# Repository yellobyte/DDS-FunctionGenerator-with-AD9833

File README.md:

# DDS Function Generator with AD9833 module #

While doing some work on Audio Amplifiers and Light Organs in 2016 I needed a simple (and not necessarily absolutely precise) **Function Generator** to generate sinus signals in the frequency range of 10Hz...30kHz and voltage levels of about 0.7...1Vrms. All devices I needed to test had input impedances in the range of ~2kOhm...20kOhm. 
  
Unfortunately I didn't call a function generator my own. So in order to have some additional fun, putting together one by myself instead of buying one on the internet was the only option. I ended up with a device able to generate output signals with the following specifications:

 - **Sinus/Triangle, amplitude 0.01 to 6.00 Vpp, frequency 1Hz to 500kHz**
 - **TTL, amplitude 5 Vpp, frequency 1Hz to 5.0 MHz**
 
 Switching waveform, output level and frequency is done with 2 front panel knobs: a pushbutton switch labelled "Select" and a simple rotary encoder with push switch labelled "Modify". The display is a standard 16x2 LCD (HD44780) having a small I2C-LCD adapter module (PCF8574 I/O expander) mounted piggyback.

All components were put into an enclosure UM 52011-L from [Bopla](https://www.bopla.de/en/enclosure-technology/product/ultramas/enclosure-with-air-vents/um-52011-l.html) which had exactly the size needed.
  
### Front side with 2 controls, 16x2 LCD display and BNC output socket: ###

The two controls allow to change signal [waveform](https://github.com/yellobyte/DDS-FunctionGenerator-with-AD9833/raw/main/Doc/SettingWaveform.mp4), output [level](https://github.com/yellobyte/DDS-FunctionGenerator-with-AD9833/raw/main/Doc/SettingLevel+SwitchingBetweenVppVrms.mp4) (Vpp resp. Vrms for sinus/triangle) and [frequency](https://github.com/yellobyte/DDS-FunctionGenerator-with-AD9833/raw/main/Doc/SettingFrequency.mp4) very quickly. Have a look at folder [**Doc**](https://github.com/yellobyte/DDS-FunctionGenerator-with-AD9833/blob/main/Doc) to find more details. 
  
## General technical info ##

The analog part of the circuitry is shielded in tin plate (an old coffee tin proved ideal for this purpose, you will recognize my favorite Italian coffee brand) to keep the output signal as clear as possible and reduce EMI. 
  
The settings for waveform/level/frequency get stored in EEPROM of the Atmega168A and therefore stay permanent even after switching the device off/on.

By default, turning the encoder knob will change the output signal immediately. For example, changing the output level from 0.5Vpp up to 6.00Vpp requires a few full turns of the knob and therefore will take a few seconds. Means the output level will rise steadily.
  
However, sometimes, when testing the automatic gain control (AGC) of audio input stages for example, it requires a signal that rises instantaneously . No problem! Switch off the device and have the encoder knob pressed for two seconds while switching power back on. After that, changing a single setting (waveform, level or frequency) on the display will not affect the output signal. Only after pressing the knob shortly (<0.5s) will the new setting appear at the output.

### Some circuit details ###
    
The DDS module (available for only a few dollars on Ebay/Ali/etc.) uses a sophisticated programmable waveform generator IC [AD9833](https://www.analog.com/en/products/ad9833.html) with 0...12.5MHz output frequency rate. 
  
Unfortunately the output pin of the AD9833 chip on the small **DDS module** shipped from Asia was galvanically isolated from the modules output pin (due to C8/C9). The quickest remedy was to bridge one of the two capacitors with a short wire, as you can see on the [**board**](https://github.com/yellobyte/DDS-FunctionGenerator-with-AD9833/raw/main/Doc/Board_V1.0_top.jpg) or below in the modules schematic. Apart from that the module was perfect for the task.

The AD9833 is written to via SPI interface. The internet provides ready to use libraries for it but I decided to use some small, quick and dirty code for only two features are needed: setting frequency & waveform.
  
The output signal of the AD9833 is unipolar and has a constant amplitude  of +38mV...+650mV over the full frequency range. The combination of Opamps IC3 + IC5 converts it to a bipolar, symmetrical signal with constant amplitude +/- 3.0V (6Vpp).  

The combination DAC1/IC6/IC7 is then used to attenuate this signal to the desired output level. The DAC IC [AD5452](https://www.analog.com/en/products/ad5452.html) contains a 12-bit R-2R-ladder and simply sets the amplification factor (better to say attenuation factor) of the combination IC6 (Opamp) + IC7 (unity gain buffer). To set the output level the selected value (0.01...6.00Vpp resp. its equivalent in Vrms) gets translated into a 12-bit value (range 0...4095) and then written to the DAC via SPI bus.

The [LMH6321](https://www.ti.com/product/LMH6321) (IC7) acts as output driver/buffer with gain=1 (unity gain) and features an  "adjustable current limit". Resistor R16 sets this limit to roughly 110mA for thermal protection in case of a short at the BNC output socket.
  
Capacitors C20/C22/C38 are not populated because the Opamp [NE5534](https://www.ti.com/product/NE5534) (IC6) showed sufficient results without them. In case you want to increase the maximum analog output frequency and try different Opamps for best results you might need them.

The two 100 Ohm resistors R9/R14 in parallel at the IC7 driver output were designed into the schematic and soldered on the board but shorted with wire in the end because the device will solely get connected to audio devices with a few 1..10kOhm input impedance and only generates audio resp. low analog frequency signals anyway. Means it will never produce RF signals, see low impedance loads, mismatches, reflections and other effects of RF hell. BTW: Having those two resistors in parallel and feeding devices with very low input impedance, e.g. 50 Ohm, would in this case halve the usable signal amplitude and subsequently force you to correct the displayed signal level on LCD, etc. Things would get complicated. 
  
Therefore wiring the IC7 driver output directly to CON2 (connected to BNC output socket) gives the function generator a very low output impedance and is appropriate under these circumstances. 

The rotary encoders two outer pins go to IMPULS-A/IMPULS-B and the middle one to ground GND. It's two switch pins go to IMPULS-SW and GND. The two pins of the separate "Select" switch go to SELECT-SW and GND on the board.  

The four pins of socket "LCD 16x2" go to the matching pins on the small **I2C-LCD board** that is mounted piggyback on the 16x2 LCD front display.

The logic gate IC8D is a low-power-Schottky Schmitt-Trigger-Inverter [74LS14](https://www.ti.com/product/SN74LS14) which acts as buffer between DDS chip and BNC output socket when a TTL output signal is selected. Firstly, its TTL signal is slightly better than the one generated by the AD9833 and secondly, a permanent short at the output would only destroy this socketed, easy replacable and inexpensive chip and not the tiny DDS chip (AD9833 in a MSOP package) soldered on the DDS module.
  
The whole device is powered by a standard 230V(prim)/2x6V(sec)/12VA transformer attached to CON1. Two jellybean voltage regulator ICs (IC2/7805 and IC4/7905) provide the needed positive/negative voltages.
  
The firmware for the device was done with VSCode/PlatformIO and is located in folder [**Software**](https://github.com/yellobyte/DDS-FunctionGenerator-with-AD9833/blob/main/Software) together with all needed fuse settings. For programming the Atmega168A I used this in-circuit [**Programmer**](https://github.com/yellobyte/USB-Atmel-In-Circuit-Programmer), connected to the 10-pin ISP socket.

### Adjusting procedure ###

For properly adjusting the analog part an oscilloscope connected to output (BNC socket) is recommended/needed. Trimmer R11 sets the maximum amplitude and trimmer R2 adjusts the offset for getting a symmetrical signal.
  
First set the output signal to Sinus, 1.000kHz and 6.00Vpp using the knobs. Then adjust the analog output signal with the two trimmers as shown below. If your osci can display Cmean, have an eye on it. Try to get it to +/-0V as close as possible for a nice symmetrical output signal without offset.

## Eagle Schematic and PCB Files ##

All relevant Eagle files (schematic, board and Gerber production files Rev 1.1) are located in folder [**EagleFiles**](https://github.com/yellobyte/DDS-FunctionGenerator-with-AD9833/blob/main/EagleFiles). The necessary Gerber files for production are zipped into file "FG with AD9833.zip".  

The pictures in folder [**Doc**](https://github.com/yellobyte/DDS-FunctionGenerator-with-AD9833/blob/main/Doc) still show board revision 1.0.   Revision 1.1 is almost identical and contains only cosmetic changes.

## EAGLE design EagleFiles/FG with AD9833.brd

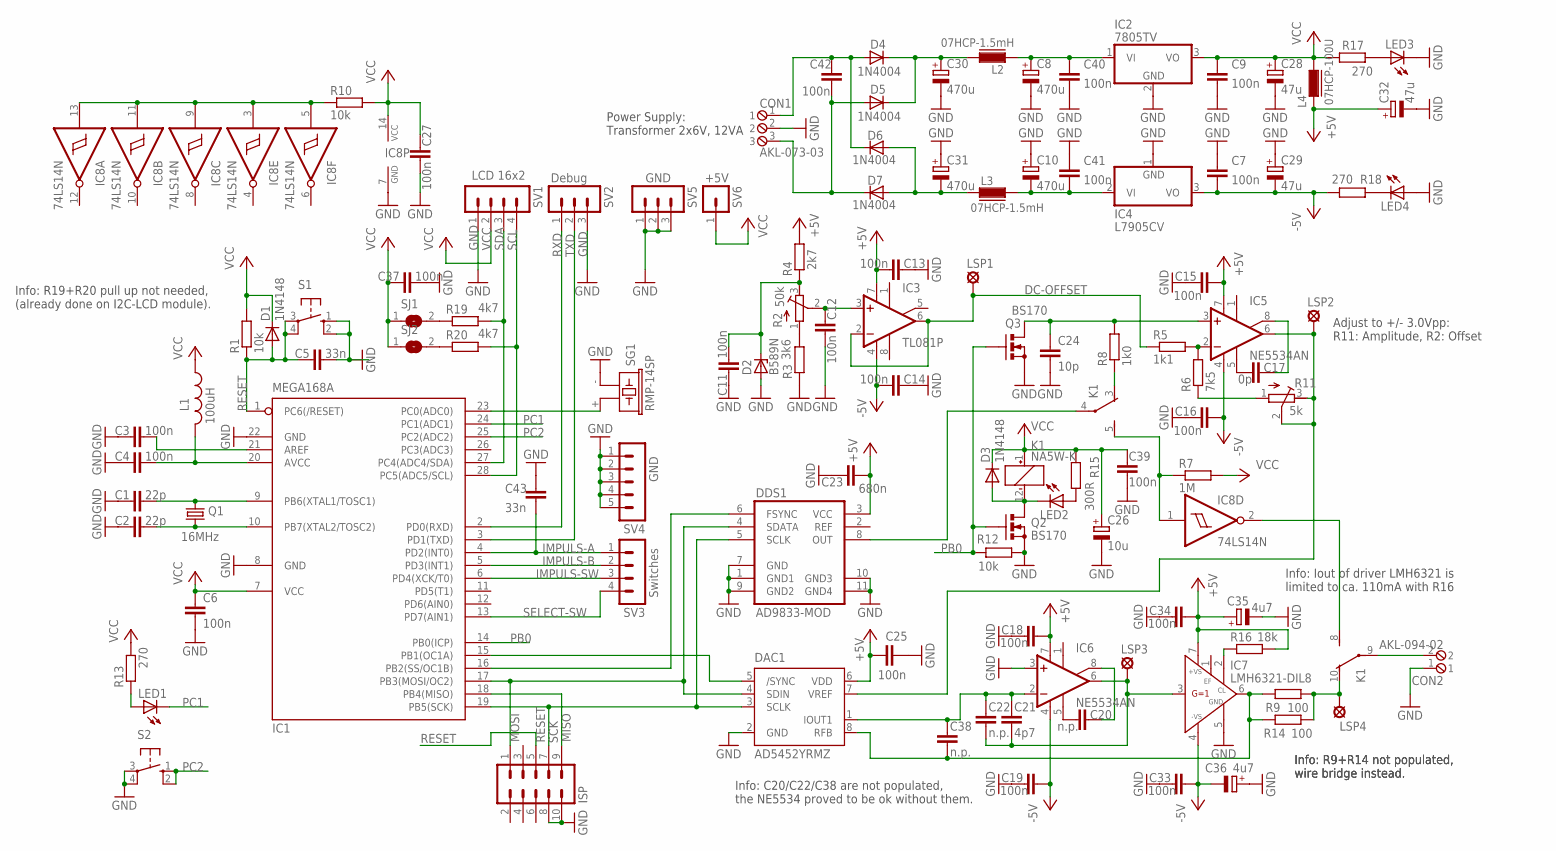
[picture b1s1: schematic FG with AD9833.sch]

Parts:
C1, C2: 22p; C025-024X044
C3, C4, C6, C7, C9, C11, C12, C13, C14, C15, C16, C18, C19, C25, C27, C33, C34, C37, C39, C40, C41, C42: 100n; C050-024X044
C5: 33n; C025-024X044
C8, C10, C30, C31: 470u; E3,5-8
C17: 0p; C025-024X044
C20, C22, C38: n.p.; C025-024X044
C21: 4p7; C025-024X044
C23: 680n; C050-024X044
C24: 10p; C025-024X044
C26: 10u; TT2D4
C28, C29, C32: 47u; E2,5-6
C35, C36: 4u7; TT2D4
C43: 33n; C050-024X044
CON1: AKL-073-03
CON2: AKL-094-02
D1: 1N4148; DO35-10
D2: B589N; TO-92H
D3: 1N4148; DO35-7
D4, D5, D6, D7: 1N4004; DO41-10
DAC1: AD5452YRMZ; MSOP08
DDS1: AD9833-MOD
IC1: MEGA168A; DIL28-3
IC2: 7805TV; TO220V
IC3: TL081P; DIL08
IC4: L7905CV; TO220-V
IC5, IC6: NE5534AN; DIL08
IC7: LMH6321-DIL8; DIL08-ADAP
IC8: 74LS14N; DIL14
ISP: ML10
K1: NA5W-K; HX
L1: 100uH; 0207/10
L2, L3: 07HCP-1.5mH; FASTRON_07HCP_INDUCTOR
L4: 07HCP-100U; FASTRON_07HCP_INDUCTOR
LED1, LED2, LED3, LED4: LED5MM
LSP1, LSP2, LSP3, LSP4: LSP11
Q1: 16MHz; HC49/S
Q2, Q3: BS170; SOT54E
R1, R10, R12: 10k; 0207/10
R2: 50k; RTRIM64W
R3: 3k6; 0207/10
R4: 2k7; 0207/10
R5: 1k1; 0207/10
R6: 7k5; 0207/10
R7: 1M; 0207/10
R8: 1k0; 0207/10
R9, R14: 100; 0207/10
R11: 5k; RTRIM64W
R13, R17, R18: 270; 0207/10
R15: 300R; 0207/10
R16: 18k; 0207/10
R19, R20: 4k7; 0207/10
S1, S2: 10-XX; B3F-10XX
SG1: RMP-14SP; F/CM12P
SJ1, SJ2: SJ
SV1, SV3: MA04-1
SV2, SV5: MA03-1
SV4: MA05-1
SV6: MA01-1

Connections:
+5V: C13.2, C15.2, C18.2, C23.2, C25.1, C32.+, C34.2, C35.+, DAC1.6 (VDD), DDS1.3 (VCC), IC3.7 (V+), IC5.7 (V+), IC6.7 (V+), IC7.7 (+VS), L4.1, R4.2, R16.2
-5V: C7.2, C14.2, C16.2, C19.2, C29.-, C33.2, C36.-, IC3.4 (V-), IC4.3 (VO), IC5.4 (V-), IC6.4 (V-), IC7.4 (-VS), R18.1
AREF: C3.2, IC1.21 (AREF)
AVCC: C4.2, IC1.20 (AVCC), L1.2
DC-OFFSET: IC3.2 (-IN), IC3.6 (OUT), LSP1.MP, R5.1
GND: C1.1, C2.1, C3.1, C4.1, C5.2, C6.2, C7.1, C8.-, C9.2, C10.+, C11.1, C12.2, C13.1, C14.1, C15.1, C16.1, C18.1, C19.1, C23.1, C24.2, C25.2, C26.-, C27.2, C28.-, C29.+, C30.-, C31.+, C32.-, C33.1, C34.1, C35.-, C36.+, C37.2, C39.1, C40.2, C41.1, C43.1, CON1.2, CON2.1, D2.2 (A), DAC1.2 (GND), DDS1.1 (GND1), DDS1.7 (GND), DDS1.9 (GND2), DDS1.10 (GND3), DDS1.11 (GND4), IC1.8 (GND), IC1.22 (GND), IC2.2 (GND), IC4.1 (GND), IC6.3 (+IN), IC7.5 (GND), IC8.7 (GND), ISP.8, ISP.10, LED3.K (C), LED4.A, Q2.S, Q3.S, R3.1, R12.1, S1.1 (S), S1.2 (S1), S2.3, S2.4 (P1), SG1.- (2), SV1.1, SV2.3, SV4.1, SV4.2, SV4.3, SV4.4, SV4.5, SV5.1, SV5.2, SV5.3
IMPULS-A: C43.2, IC1.4 (PD2(INT0)), SV3.1
IMPULS-B: IC1.5 (PD3(INT1)), SV3.2
IMPULS-SW: IC1.6 (PD4(XCK/T0)), SV3.3
MISO: IC1.18 (PB4(MISO)), ISP.9
MOSI: DAC1.4 (SDIN), DDS1.4 (SDATA), IC1.17 (PB3(MOSI/OC2)), ISP.1
unnamed: R2.1 (A), R3.2
unnamed: DDS1.6 (FSYNC), IC1.16 (PB2(SS/OC1B))
unnamed: DAC1.5 (/SYNC), IC1.15 (PB1(OC1A))
unnamed: IC5.2 (-IN), R5.2, R6.2
unnamed: C8.+, C40.1, IC2.1 (VI), L2.1
unnamed: IC8.1 (I), K1.5 (S), R7.1
unnamed: C31.-, D6.A, D7.A, L3.1
unnamed: DDS1.8 (OUT), K1.4
unnamed: C17.1, IC5.5 (CMP)
unnamed: C17.2, IC5.8 (ON/CMP)
unnamed: K1.3 (O), R8.1
unnamed: R6.1, R11.1 (A)
unnamed: LED1.A, R13.1
unnamed: C30.+, D4.C, D5.C, L2.2
unnamed: C10.-, C41.2, IC4.2 (VI), L3.2
unnamed: C42.1, CON1.1, D4.A, D6.C
unnamed: C21.2, C22.2, IC6.6 (OUT), IC7.3 (IN), LSP3.MP
unnamed: IC1.23 (PC0(ADC0)), SG1.+ (1)
unnamed: C42.2, CON1.3, D5.A, D7.C
unnamed: IC8.3 (I), IC8.5 (I), IC8.9 (I), IC8.11 (I), IC8.13 (I), R10.1
unnamed: IC7.2 (CL), R16.1
unnamed: C38.2, DAC1.8 (RFB), IC7.6 (OUT), R9.2, R14.2
unnamed: K1.10 (O), LSP4.MP, R9.1, R14.1
unnamed: LED3.A, R17.1
unnamed: LED4.K (C), R18.2
unnamed: C20.1, IC6.5 (CMP)
unnamed: R19.1, SJ1.2
unnamed: C20.2, IC6.8 (ON/CMP)
unnamed: C21.1, C22.1, C38.1, DAC1.1 (IOUT1), IC6.2 (-IN)
unnamed: R20.1, SJ2.2
unnamed: CON2.2, K1.9
unnamed: C24.1, IC5.3 (+IN), Q3.D, R8.2
unnamed: C12.1, IC3.3 (+IN), R2.2 (S)
unnamed: C11.2, D2.1 (C), R2.3 (E), R4.1
unnamed: D3.A, K1.12 (-), LED2.K (C), Q2.D
unnamed: IC8.2 (O), K1.8 (S)
unnamed: LED2.A, R15.2
OSC1: C1.2, IC1.9 (PB6(XTAL1/TOSC1)), Q1.2
OSC2: C2.2, IC1.10 (PB7(XTAL2/TOSC2)), Q1.1
PB0: IC1.14 (PB0(ICP)), Q2.G, Q3.G, R12.2
PC1: IC1.24 (PC1(ADC1)), LED1.K (C)
PC2: IC1.25 (PC2(ADC2)), S2.1 (S), S2.2 (S1)
RESET: C5.1, D1.A, IC1.1 (PC6(/RESET)), ISP.5, R1.1, S1.3, S1.4 (P1)
RXD: IC1.2 (PD0(RXD)), SV2.1
SCK: DAC1.3 (SCLK), DDS1.5 (SCLK), IC1.19 (PB5(SCK)), ISP.7
SCL: IC1.28 (PC5(ADC5/SCL)), R20.2, SV1.4
SDA: IC1.27 (PC4(ADC4/SDA)), R19.2, SV1.3
SELECT-SW: IC1.13 (PD7(AIN1)), SV3.4
TXD: IC1.3 (PD1(TXD)), SV2.2
VCC: C6.1, C9.1, C26.+, C27.1, C28.+, C37.1, C39.2, D1.C, D3.C, IC1.7 (VCC), IC2.3 (VO), IC8.14 (VCC), K1.1 (+), L1.1, L4.2, R1.2, R7.2, R10.2, R13.2, R15.1, R17.2, SJ1.1, SJ2.1, SV1.2, SV6.1
VREF: DAC1.7 (VREF), IC5.6 (OUT), LSP2.MP, R11.2 (S), R11.3 (E)

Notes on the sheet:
LCD 16x2
Switches
GND
Debug
Info: R19+R20 pull up not needed, (already done on I2C-LCD module).
+5V
Adjust to +/- 3.0Vpp: R11: Amplitude, R2: Offset
Info: R9+R14 not populated, wire bridge instead.
Power Supply: Transformer 2x6V, 12VA
Info: C20/C22/C38 are not populated, the NE5534 proved to be ok without them.
Info: Iout of driver LMH6321 is limited to ca. 110mA with R16

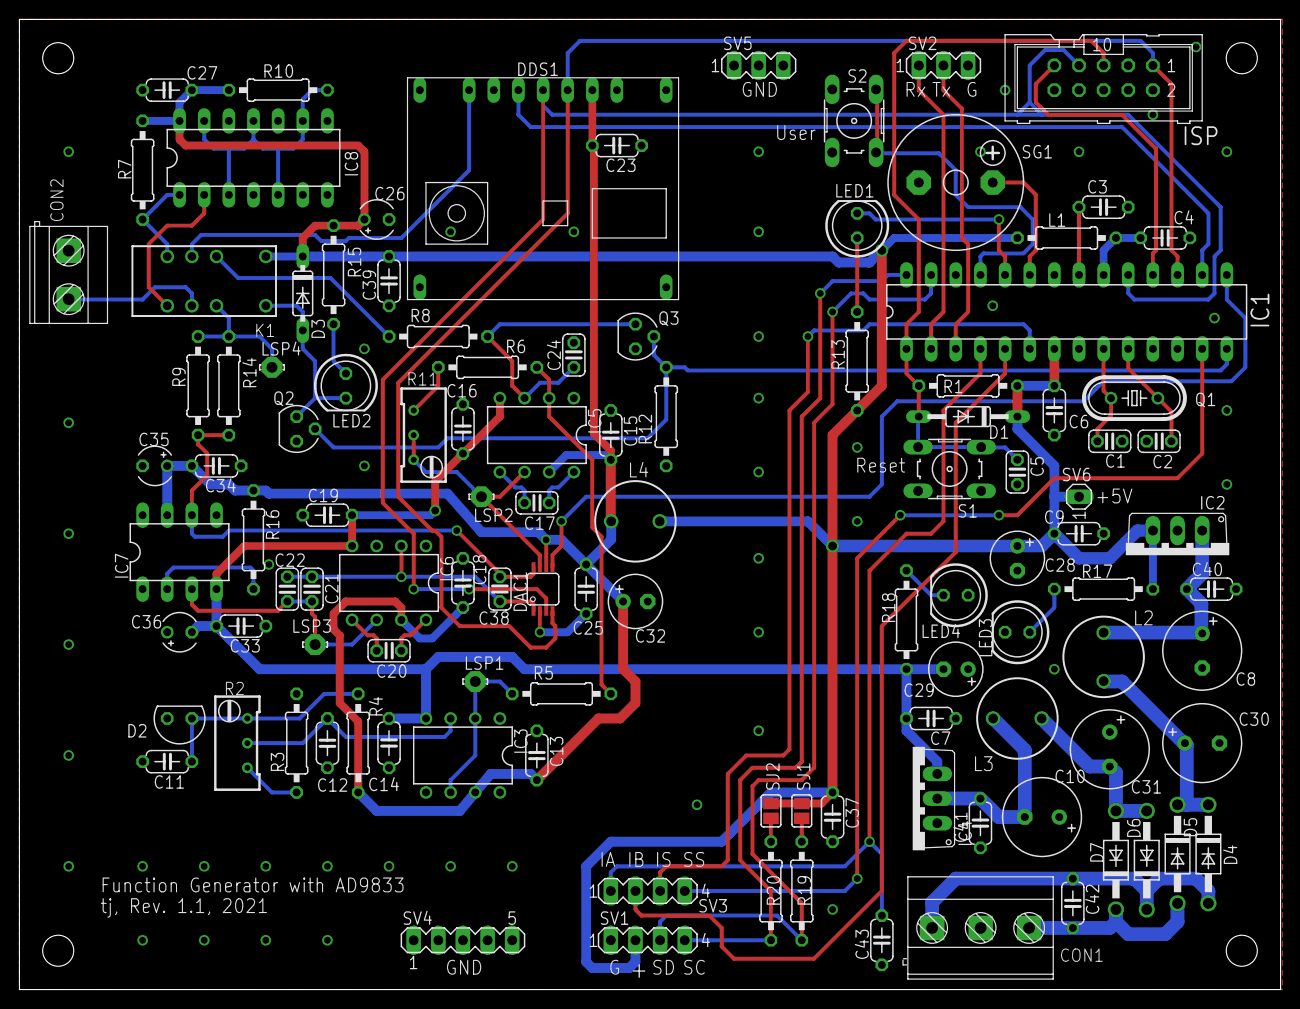
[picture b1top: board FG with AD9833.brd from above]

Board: 2 copper layers, 130.0 x 100.0 mm, 110 parts (0 on the bottom side), 62 nets.

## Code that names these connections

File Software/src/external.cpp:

/*
 * EXTERNAL.CPP: definitions and functions for the AD9833 function generator
 *
 * Created: June 2016
 *          2021/10/01 possibility to set output level in Vrms added
 * Author : ThJ (yellobyte@bluewin.ch)
*/

#include <Arduino.h>
#include <SPI.h>
#include <LiquidCrystal_I2C.h>
#include "ad9833.h"
#include "external.h"

#define PIN_RELAY         PIN_PB0
#define PIN_BUZZER        PIN_PC0
#define PIN_ENCODERA      PIN_PD2
#define PIN_ENCODERB      PIN_PD3
#define PIN_ENCODERBUTTON PIN_PD4
#define PIN_PUSHBUTTON    PIN_PD7
#define PIN_AD5452_CS     PIN_PB1
#define SPI_AD5452        SPISettings(2000000, MSBFIRST, SPI_MODE2)

extern LiquidCrystal_I2C  lcd;
extern uint8_t            outputLevelStepSize;

volatile uint8_t rotaryImpulseLeft = 0;
volatile uint8_t rotaryImpulseRight = 0;

//
// functions for displaying frequency, waveform and output level on 16x2 LCD display
//
void EXTDisplayFrequency(uint32_t frequ, uint8_t leadingZeros)
{
  uint8_t  i;
  uint8_t	 digit[7];
  uint32_t temp;

  temp = (frequ < 10000000) ? frequ : 9999999;
  for (i = 0; i < 7; i++) digit[i] = 0; // clear array
  for (i = 0; temp > 0; i++) {
    digit[6-i] = (uint8_t)(temp % 10);
    temp = temp / 10;
  }
  lcd.setCursor(4,0);
  for (i = 0; i < 7; i++) {
    if (i == 0) {
      if ( digit[0] != 0 ) {
        lcd.print((char)(48+digit[0]));
        lcd.print((char)'.'); 
      }
      else {
         lcd.print((char)' ');
         lcd.print((char)' ');
      }
    }
    else if ( i == 1 && digit[0] == 0 && digit[1] == 0 && !(leadingZeros == 2) ) {
       lcd.print((char)' ');
    }
    else if ( i == 2 && digit[0] == 0 && digit[1] == 0 && digit[2] == 0 && leadingZeros == 0 ) {
       lcd.print((char)' ');
    }
    else if (i == 3) {
      lcd.print((char)(48+digit[i]));
      lcd.print((char)'.'); 
    }
    else {
      lcd.print((char)(48+digit[i])); 
    }
  }
  lcd.print((char)'k');
  lcd.print((char)'H');
  lcd.print((char)'z');
}

void EXTDisplayLevel(uint16_t outputLevel, uint8_t outputLevelMode)
{
  uint8_t  i, digits[3];
  uint16_t temp = outputLevel;

  for (i=0; i<3; i++) digits[i] = 0;
  digits[2] = (uint8_t)(temp % 10);
  temp /= 10;
  digits[1] = (uint8_t)(temp % 10);
  temp /= 10;
  digits[0] = (uint8_t)(temp % 10);
  lcd.setCursor(9,1);
  lcd.print((char)(48+digits[0]));
  lcd.print((char)'.');
  lcd.print((char)(48+digits[1]));
  lcd.print((char)(48+digits[2]));

  lcd.setCursor(13,1);
  lcd.print(outputLevelMode ? "Vpp" : "Vrm");
}

void EXTDisplayWaveform(uint8_t waveform)
{
  switch (waveform){
    case SINUS:
      lcd.setCursor(0,1);
      lcd.print("SINUS   "); 
      break;
    case SQUARE:
      lcd.setCursor(0,1);
      lcd.print("SQUARE    5V-TTL"); 
      break;
    case TRIANGLE:
      lcd.setCursor(0,1);
      lcd.print("TRIANGLE");
      break;
    default:
      break;
  }	
}

//
// functions for handling the relais
//
void EXTRelaisInit(void)
{
  pinMode(PIN_RELAY, OUTPUT);   
  digitalWrite(PIN_RELAY, LOW);     // relais off
}

void EXTRelaisOnOff(uint8_t setting)
{
  if ( setting == RELAIS_ON )
    digitalWrite(PIN_RELAY, HIGH);  // relais on
  else
    digitalWrite(PIN_RELAY, LOW);   // relais off
}

//
// functions for handling the buzzer
//
void EXTBuzzerInit(void)
{
  pinMode(PIN_BUZZER, OUTPUT);   
  digitalWrite(PIN_BUZZER, LOW);   // buzzer off
}

void EXTBuzzerRing(uint16_t ms)
{
  digitalWrite(PIN_BUZZER, HIGH);  // buzzer on
  delay(ms);					             // Buzzer x ms aktiv
  digitalWrite(PIN_BUZZER, LOW);   // buzzer off
}

//
// functions for handling the select button
//
void EXTSelectSwitchInit(void)
{
  pinMode(PIN_PUSHBUTTON, INPUT_PULLUP);   
}

uint8_t EXTSelectSwitchCheck(void)
{
  // function returns: 1...button was pressed, 0...otherwise
  static uint8_t oldStatus = 1;                         // default - switch not pressed
  uint8_t	status, ret = 0;
 
  status = digitalRead(PIN_PUSHBUTTON);
  if (!status && oldStatus) {                           // any input change ?
    for (uint8_t n = 0; n < 5; ) {
      delayMicroseconds(200);
      n = !digitalRead(PIN_PUSHBUTTON) ? n + 1 : 0;
    }
    // since 5 * 200us = 1ms no change at input
    ret = 1;
    oldStatus = status;                                 // remember last stable signal
  }
  else {
    oldStatus = status;                                 // remember last reading
  }  
  return(ret);
}

//
// functions handling the rotary encoder & button
//
static void impulsIrq()
{
  // PIN_ENCODERB==1 -> left turn,  PIN_ENCODERB==0 -> right turn
  if (digitalRead(PIN_ENCODERB)) {
    rotaryImpulseLeft++;
  }
  else {
    rotaryImpulseRight++;
  }
  // trailing spikes will be ignored for some time
  delayMicroseconds(50);
}

void EXTRotaryInit(void)
{
  pinMode(PIN_ENCODERBUTTON, INPUT_PULLUP);
  pinMode(PIN_ENCODERB, INPUT_PULLUP);
  pinMode(PIN_ENCODERA, INPUT_PULLUP);
  attachInterrupt(digitalPinToInterrupt(PIN_ENCODERA),impulsIrq,FALLING);
}

buttonEvent EXTRotaryButtonCheck(void)
{
  // function returns: 1...short press (<0.5s), 2...long press (>0.5s-3s), 0...otherwise
  static uint8_t oldStatus = 1;                             // default - button not pressed
  uint8_t	status;
  buttonEvent event = idle;
 
  status = digitalRead(PIN_ENCODERBUTTON);
  if (!status && oldStatus) {                               // falling edge ?
    for (uint8_t n = 0; n < 5; ) {                          // wait for stable low
      delayMicroseconds(200);
      n = !digitalRead(PIN_ENCODERBUTTON) ? n + 1 : 0;
    }
    for (uint16_t n = 1; status == LOW && n < 50; ) {       // wait for rising edge
      delay(100);
      if (!(status = digitalRead(PIN_ENCODERBUTTON))) n++;  // input still low -> knob still pressed
      else event = (n < 5) ? shortPress : longPress;        // input high again -> knob was released
    }
    oldStatus = status;                                     // remember last stable signal
  }
  else {
    oldStatus = status;                                     // remember last reading
  }
  return(event);
}

int8_t EXTRotaryImpulseCheck(void)
{
  // function returns: -1...knob was turned left, 1...knob was turned right, 0...knob was idle
  uint8_t ret = 0;
  if (rotaryImpulseLeft) {
    ret = -1;
    rotaryImpulseLeft--;
  }
  else if (rotaryImpulseRight) {
    ret = 1;
    rotaryImpulseRight--;
  }
  return(ret);
}

//
// functions handling the DAC AD5452 for setting output voltage level when SINUS or TRIANGLE
// (the DAC R-2R ladder is used to set the amplification ratio of OpAmp IC6, the output level range
// is +/- 3V (6Vpp) at maximum, adjusted with R11 at BNC output)
//
void EXTDacInit(void)
{
  SPI.begin();
}

void EXTDacSetLevel(uint16_t outputLevel, uint8_t outputWaveform, uint8_t outputLevelMode)
{
  uint16_t temp1, regist;
  double temp2;

  if (outputLevelMode) {
    // output level already represents Vpp
    temp1 = outputLevel;
  }
  else {
    // conversion Vrms to Vpp required (adding 0.5 for minimizing conversion error)
    temp1 = (uint16_t)(((double)outputLevel * 2 * (double)((outputWaveform == SINUS) ? SQRT2 : SQRT3)) + 0.5);
  }
  // final check 
  temp1 = (OUTPUT_LEVEL_VPP_MAX < temp1) ? OUTPUT_LEVEL_VPP_MAX : temp1;

  // at this point temp1 always represents the Vpp output level which must be converted
  // into a value between 0 and 4095 (DAC R-2R ladder setting)
  temp2 = ((double)temp1/(double)OUTPUT_LEVEL_VPP_MAX);
  regist = (uint16_t)(temp2 * (double)0xFFF);
  regist = regist << 2;
  regist &= 0x3FFF;                       // clearing control bits C1/C0 in AD5452

  // loading a word to the DAC (D15/D14...control bits, D13-D2...data bits, D1/D0...not used))
  SPI.beginTransaction(SPI_AD5452);
  digitalWrite(PIN_AD5452_CS, LOW);       // set select signal LOW for DAC AD5452
  SPI.transfer((uint8_t)(regist >> 8));
  SPI.transfer((uint8_t)(regist & 255));
  digitalWrite(PIN_AD5452_CS, HIGH);      // set select signal HIGH for DAC AD5452
  SPI.endTransaction();  
}

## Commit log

2021-10-04 Changing Readme.md
